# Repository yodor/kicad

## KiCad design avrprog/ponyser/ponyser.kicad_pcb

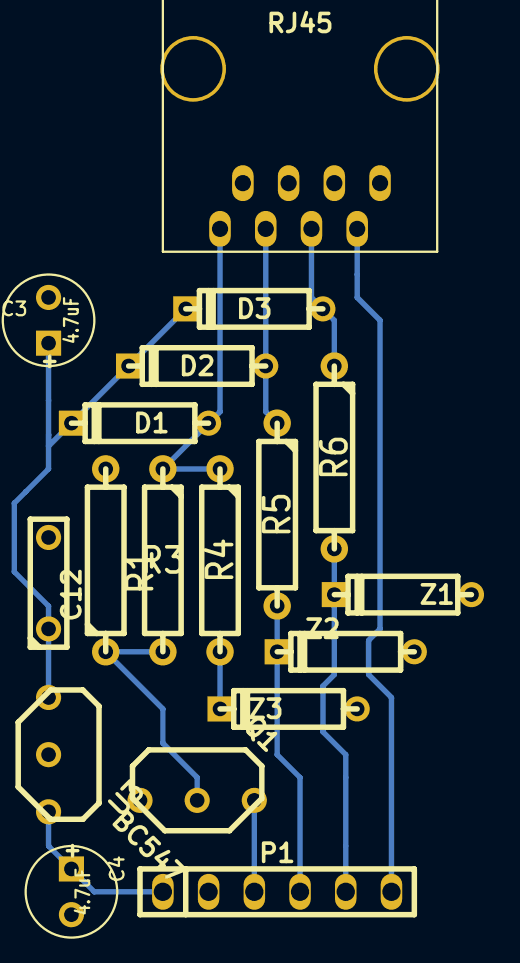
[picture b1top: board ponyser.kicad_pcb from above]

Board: 2 copper layers, 18 parts (0 on the bottom side), 12 nets.

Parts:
C3, C4: 4.7uF; C1V5
C12: 100nF; C2
D1, D2, D3: DIODE; D3
J1: RJ45; RJ45_8
P1: CONN_6; PIN_ARRAY-6X1
Q1: BC547; TO92
R1: 15K; R4
R3: 10K; R4
R4, R5, R6: 4.7K; R4
U3: LM2936Z-5; LM2931
Z1, Z2, Z3: 5.1V; D3

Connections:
GND: C3.2, C4.2, C12.2, J1.1, J1.3, J1.5, J1.7, P1.1, Q1.1, R1.2, U3.GND, Z1.1, Z2.1, Z3.1
unnamed: D1.1, J1.8, R3.1, R4.1
unnamed: Q1.2, R1.1, R3.2
unnamed: P1.6, Q1.3
unnamed: J1.2, P1.5
unnamed: D2.1, J1.6, R5.1
unnamed: D3.1, J1.4, R6.1
unnamed: C3.1, C12.1, D1.2, D2.2, D3.2, U3.VI
unnamed: P1.3, R6.2, Z1.2
unnamed: P1.4, R5.2, Z2.2
unnamed: R4.2, Z3.2
VCC: C4.1, P1.2, U3.VO

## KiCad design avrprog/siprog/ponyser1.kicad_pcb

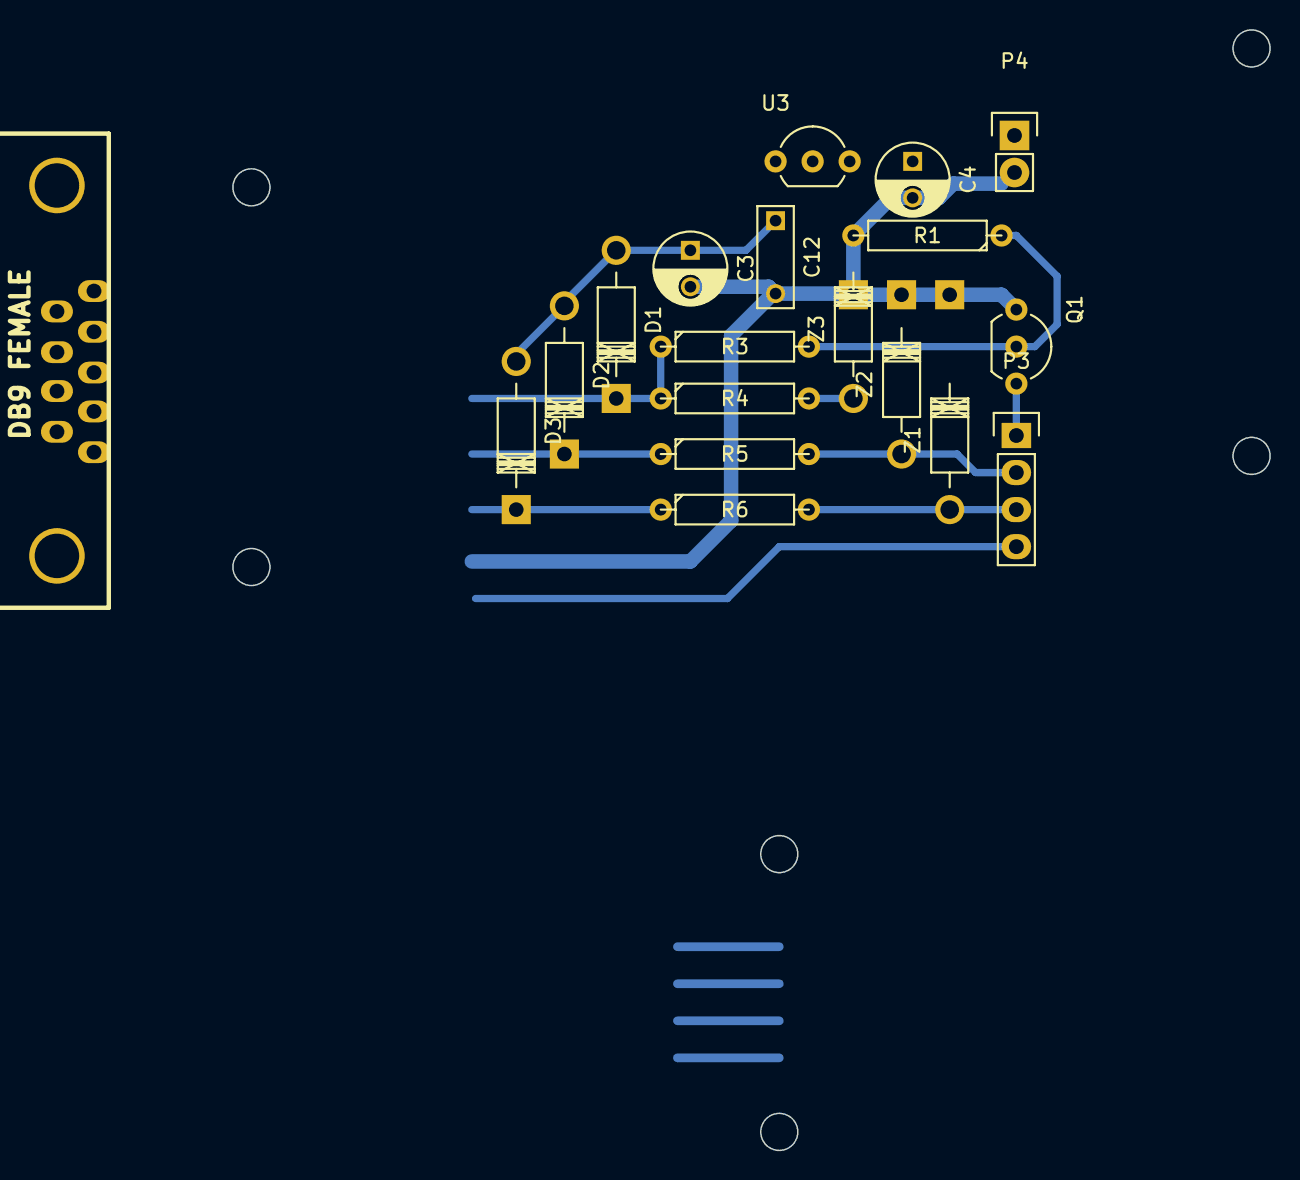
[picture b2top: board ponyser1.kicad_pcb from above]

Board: 2 copper layers, 71.1 x 76.8 mm, 19 parts (0 on the bottom side), 12 nets.

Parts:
C3, C4: 47uF; C_Radial_D5_L11_P2.5
C12: 100nF; C_Rect_L7_W2.5_P5
D1: 1N4148; Diode_DO-41_SOD81_Horizontal_RM10
D2, D3: DIODE; Diode_DO-41_SOD81_Horizontal_RM10
J1: DB9 FEMALE; DB9MC
P3: CONN_4; Pin_Header_Straight_1x04
P4: CONN_2; Pin_Header_Straight_1x02
Q1: BC547; TO-92_Inline_Wide
R1: 15K; R4
R3: 10K; R4
R4, R5, R6: 4.7K; R4
U3: LM2936Z-5; TO-92_Inline_Wide
Z1, Z2, Z3: 5.1V; Diode_DO-41_SOD81_Horizontal_RM10

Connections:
/CTS: J1.8, P3.4
/DTR: D3.1, J1.4, R6.1
/MOSI: P3.3, R6.2, Z1.2
/RST: P3.1, Q1.3
/RTS: D2.1, J1.7, R5.1
/SCK: P3.2, R5.2, Z2.2
/TX: D1.1, J1.3, R3.1, R4.1
GND: C3.2, C4.2, C12.2, J1.5, P4.2, Q1.1, R1.2, Z1.1, Z2.1, Z3.1
unnamed: C3.1, C12.1, D1.2, D2.2, D3.2
unnamed: Q1.2, R1.1, R3.2
unnamed: R4.2, Z3.2
VCC: C4.1, P4.1

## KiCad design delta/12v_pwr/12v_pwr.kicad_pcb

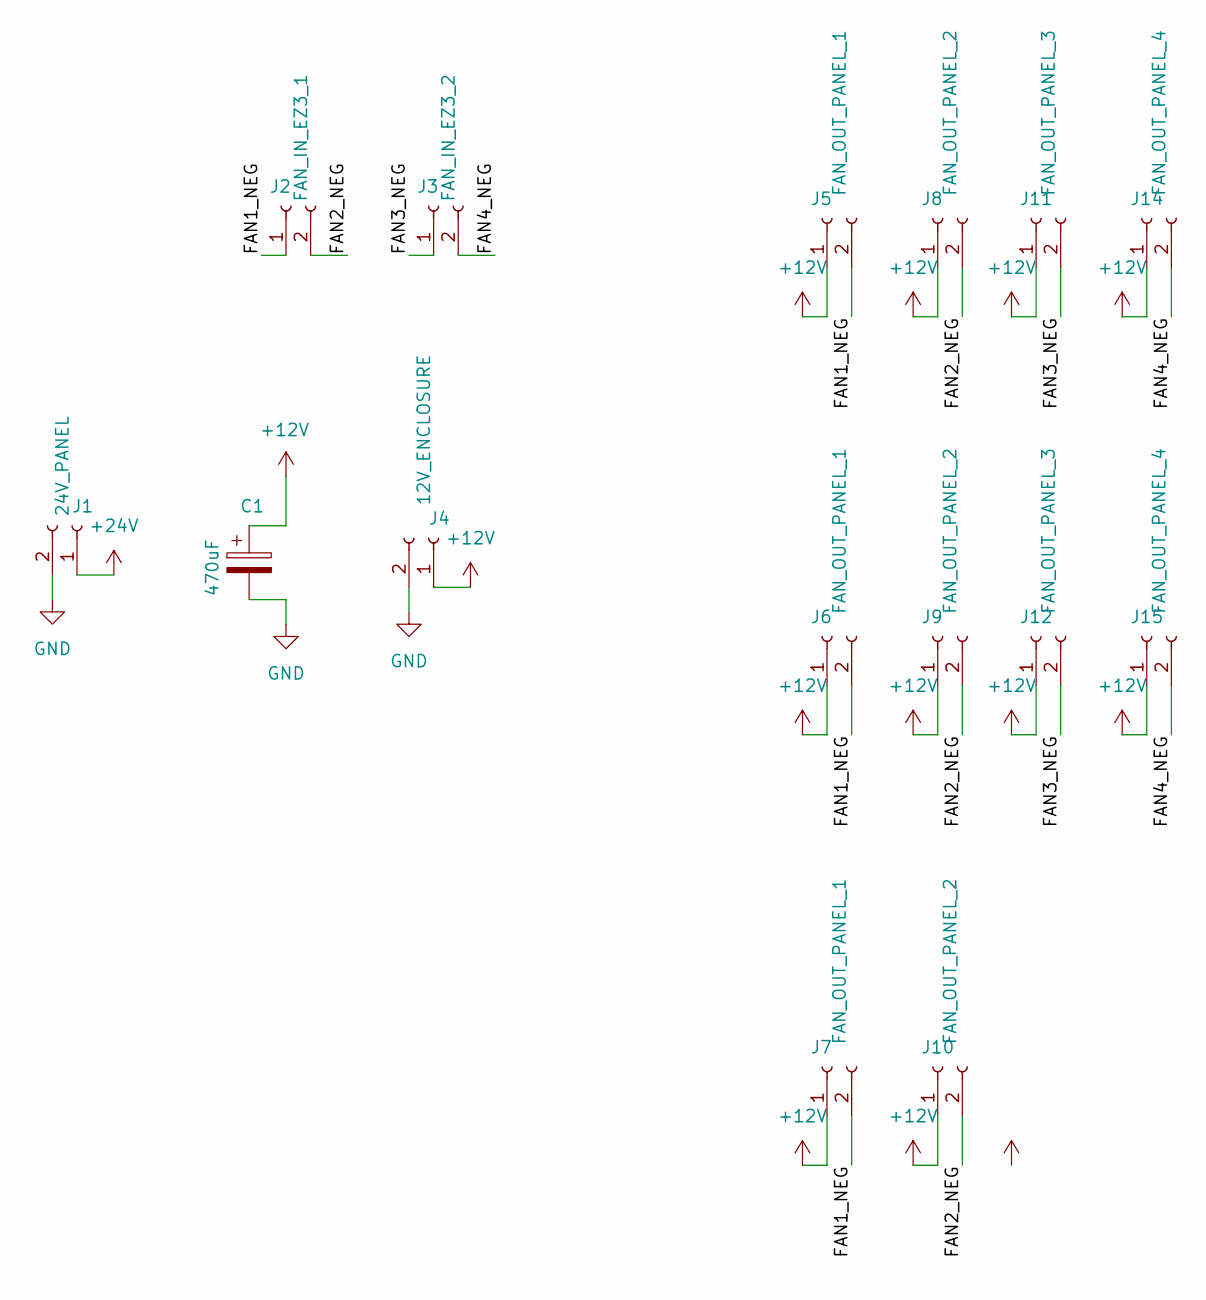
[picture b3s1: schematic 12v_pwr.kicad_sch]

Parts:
C1: 470uF; CP_Radial_D10.0mm_P5.00mm
J1: 24V_PANEL; TerminalBlock_Phoenix_PT-1,5-2-5.0-H_1x02_P5.00mm_Horizontal
J2: FAN_IN_EZ3_1; JST_XH_B2B-XH-A_1x02_P2.50mm_Vertical
J3: FAN_IN_EZ3_2; JST_XH_B2B-XH-A_1x02_P2.50mm_Vertical
J4: 12V_ENCLOSURE; TerminalBlock_Phoenix_PT-1,5-2-5.0-H_1x02_P5.00mm_Horizontal
J5, J6, J7: FAN_OUT_PANEL_1; JST_XH_B2B-XH-A_1x02_P2.50mm_Vertical
J8, J9, J10: FAN_OUT_PANEL_2; JST_XH_B2B-XH-A_1x02_P2.50mm_Vertical
J11, J12: FAN_OUT_PANEL_3; JST_XH_B2B-XH-A_1x02_P2.50mm_Vertical
J14, J15: FAN_OUT_PANEL_4; JST_XH_B2B-XH-A_1x02_P2.50mm_Vertical

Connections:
+12V: C1.1, J4.1, J5.1, J6.1, J7.1, J8.1, J9.1, J10.1, J11.1, J12.1, J14.1, J15.1
+24V: J1.1
/FAN1_NEG: J2.1, J5.2, J6.2, J7.2
/FAN2_NEG: J2.2, J8.2, J9.2, J10.2
/FAN3_NEG: J3.1, J11.2, J12.2
/FAN4_NEG: J3.2, J14.2, J15.2
GND: C1.2, J1.2, J4.2

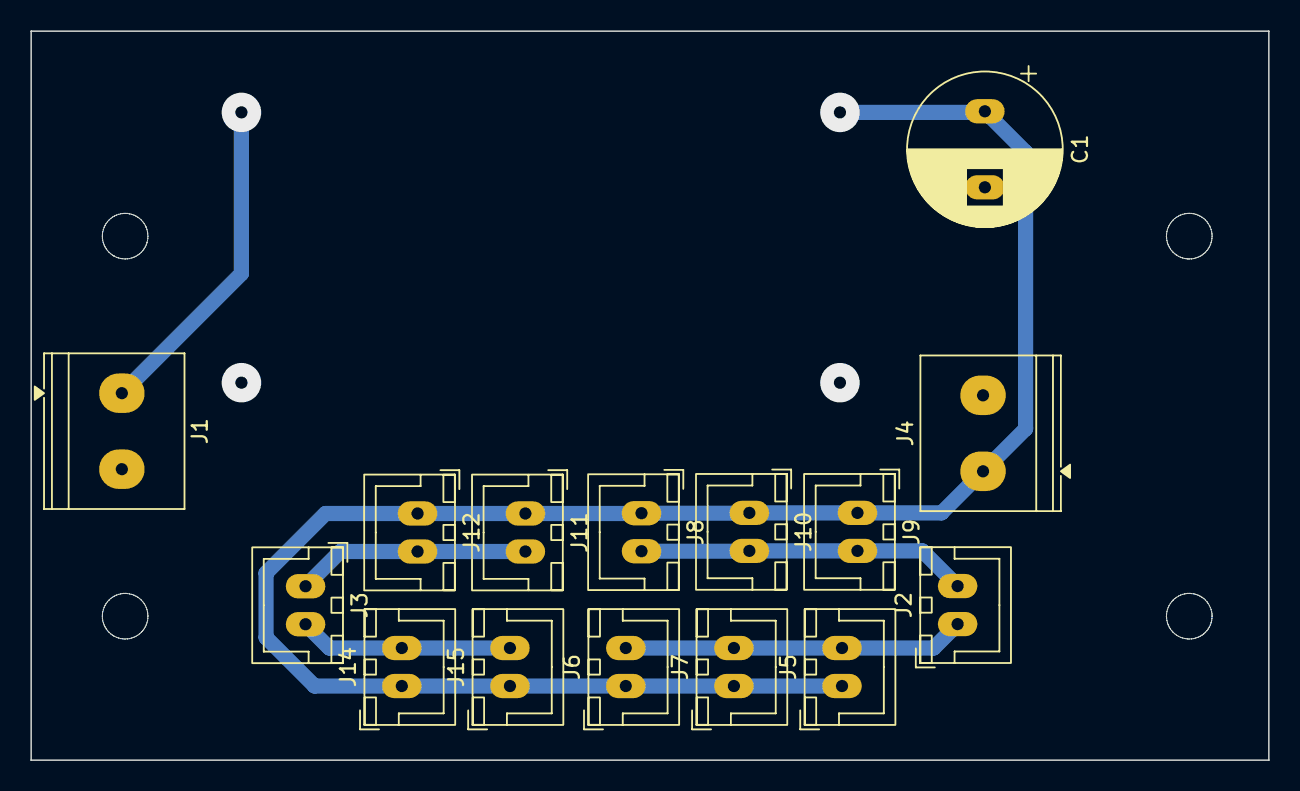
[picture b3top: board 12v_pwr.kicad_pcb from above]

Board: 2 copper layers, 81.4 x 48.0 mm, 15 parts (0 on the bottom side), 6 nets.

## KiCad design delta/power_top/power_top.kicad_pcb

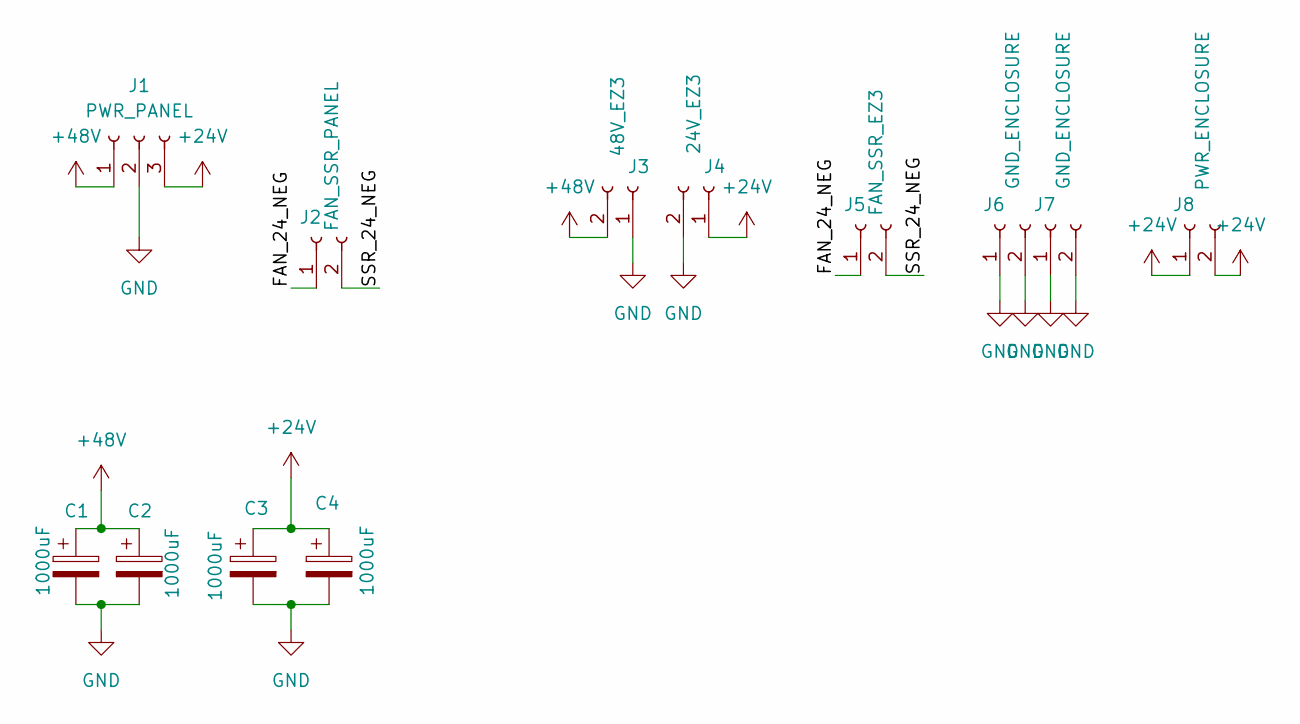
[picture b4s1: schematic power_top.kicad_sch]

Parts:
C1, C2, C3, C4: 1000uF; CP_Radial_D16.0mm_P7.50mm
J1: PWR_PANEL; TE_826576-3_1x03_P3.96mm_Vertical
J2: FAN_SSR_PANEL; TE_826576-2_1x02_P3.96mm_Vertical
J3: 48V_EZ3; TE_826576-2_1x02_P3.96mm_Vertical
J4: 24V_EZ3; TE_826576-2_1x02_P3.96mm_Vertical
J5: FAN_SSR_EZ3; JST_XH_B2B-XH-A_1x02_P2.50mm_Vertical
J6, J7: GND_ENCLOSURE; TE_826576-2_1x02_P3.96mm_Vertical
J8: PWR_ENCLOSURE; TE_826576-2_1x02_P3.96mm_Vertical

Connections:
+24V: C3.1, C4.1, J1.3, J4.1, J8.1, J8.2
+48V: C1.1, C2.1, J1.1, J3.2
/FAN_24_NEG: J2.1, J5.1
/SSR_24_NEG: J2.2, J5.2
GND: C1.2, C2.2, C3.2, C4.2, J1.2, J3.1, J4.2, J6.1, J6.2, J7.1, J7.2

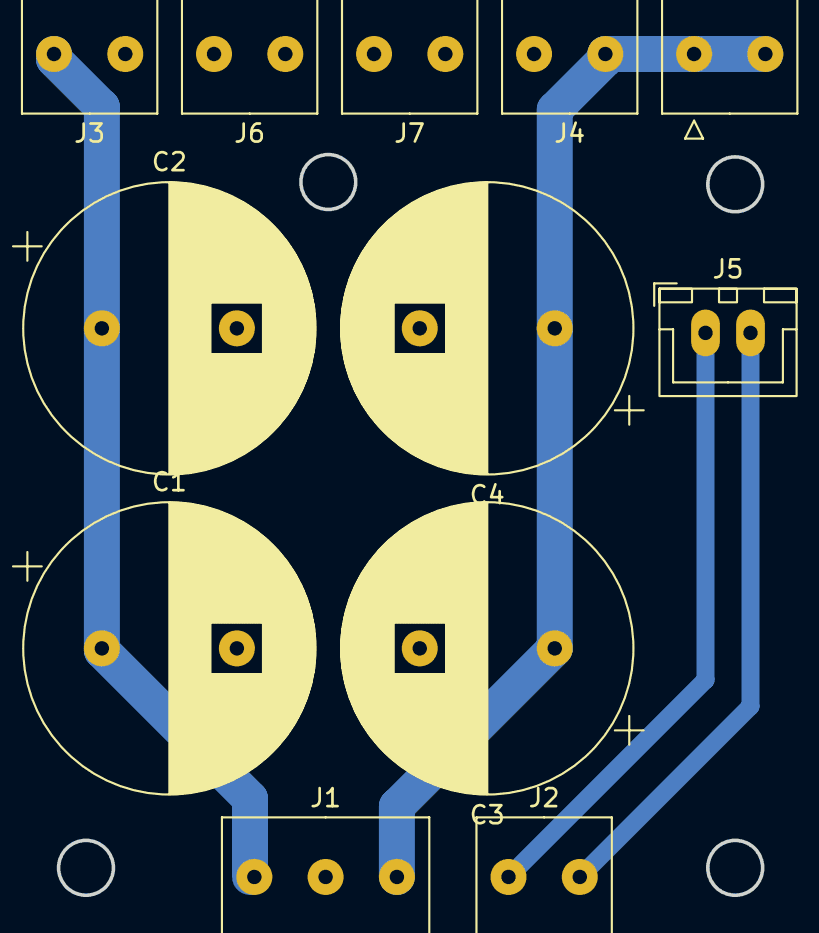
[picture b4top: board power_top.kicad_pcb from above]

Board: 2 copper layers, 12 parts (0 on the bottom side), 5 nets.

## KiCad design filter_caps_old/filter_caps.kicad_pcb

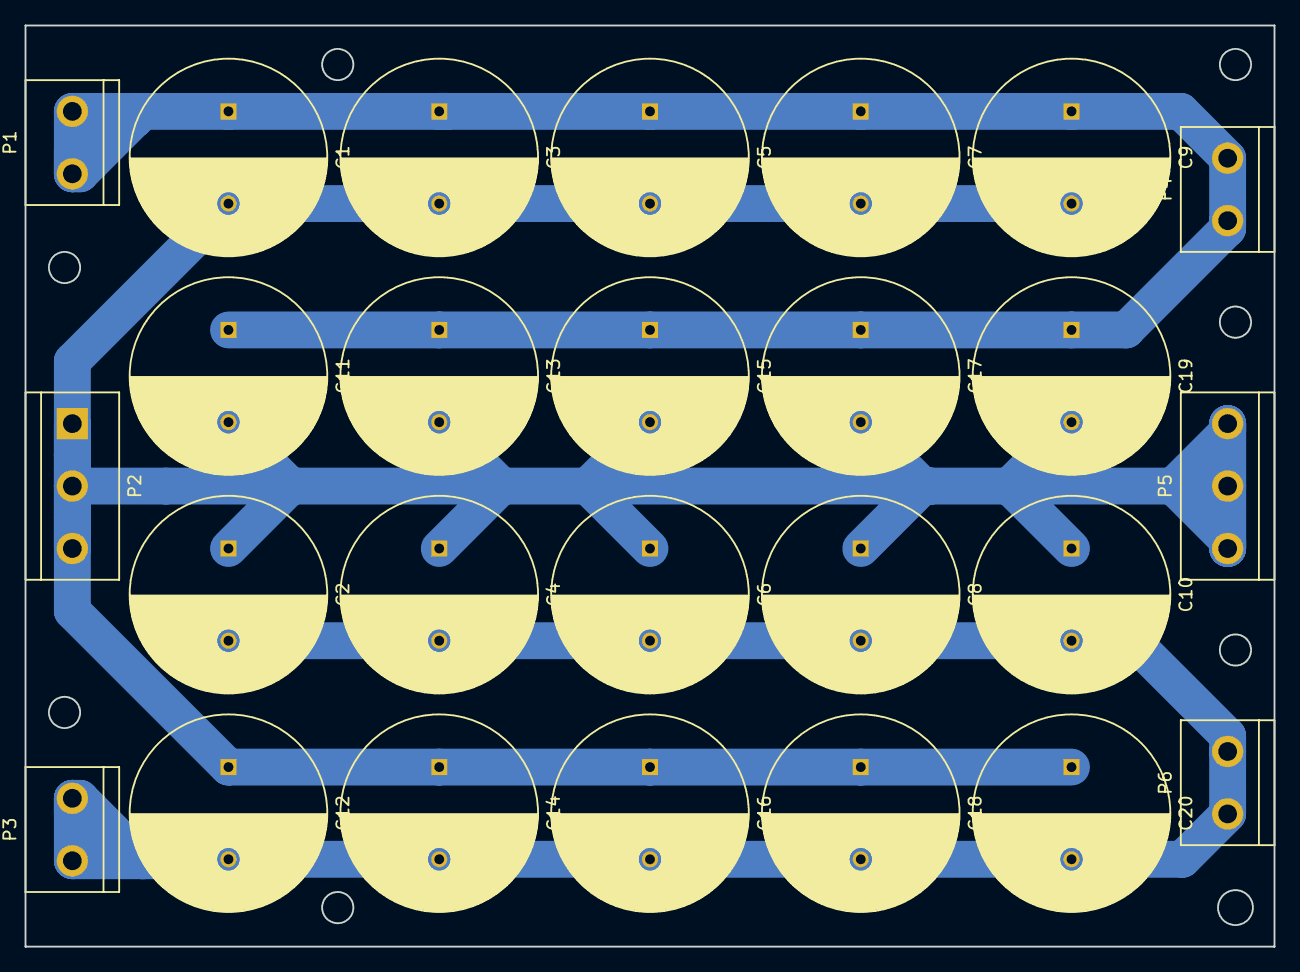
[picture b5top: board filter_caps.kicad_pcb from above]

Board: 2 copper layers, 101.6 x 74.9 mm, 26 parts (0 on the bottom side), 3 nets.

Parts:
C1, C2, C3, C4, C5, C6, C7, C8, C9, C10, C11, C12, C13, C14, C15, C16, C17, C18, C19, C20: CP; C_Radial_D16_L25_P7.5
P1, P3, P4, P6: CONN_01X02; bornier2
P2, P5: CONN_01X03; bornier3

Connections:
/0: C1.2, C2.1, C3.2, C4.1, C5.2, C6.1, C7.2, C8.1, C9.2, C10.1, C11.2, C12.1, C13.2, C14.1, C15.2, C16.1, C17.2, C18.1, C19.2, C20.1, P2.1, P2.2, P2.3, P5.1, P5.2, P5.3
/V+: C1.1, C3.1, C5.1, C7.1, C9.1, C11.1, C13.1, C15.1, C17.1, C19.1, P1.1, P1.2, P4.1, P4.2
/V-: C2.2, C4.2, C6.2, C8.2, C10.2, C12.2, C14.2, C16.2, C18.2, C20.2, P3.1, P3.2, P6.1, P6.2

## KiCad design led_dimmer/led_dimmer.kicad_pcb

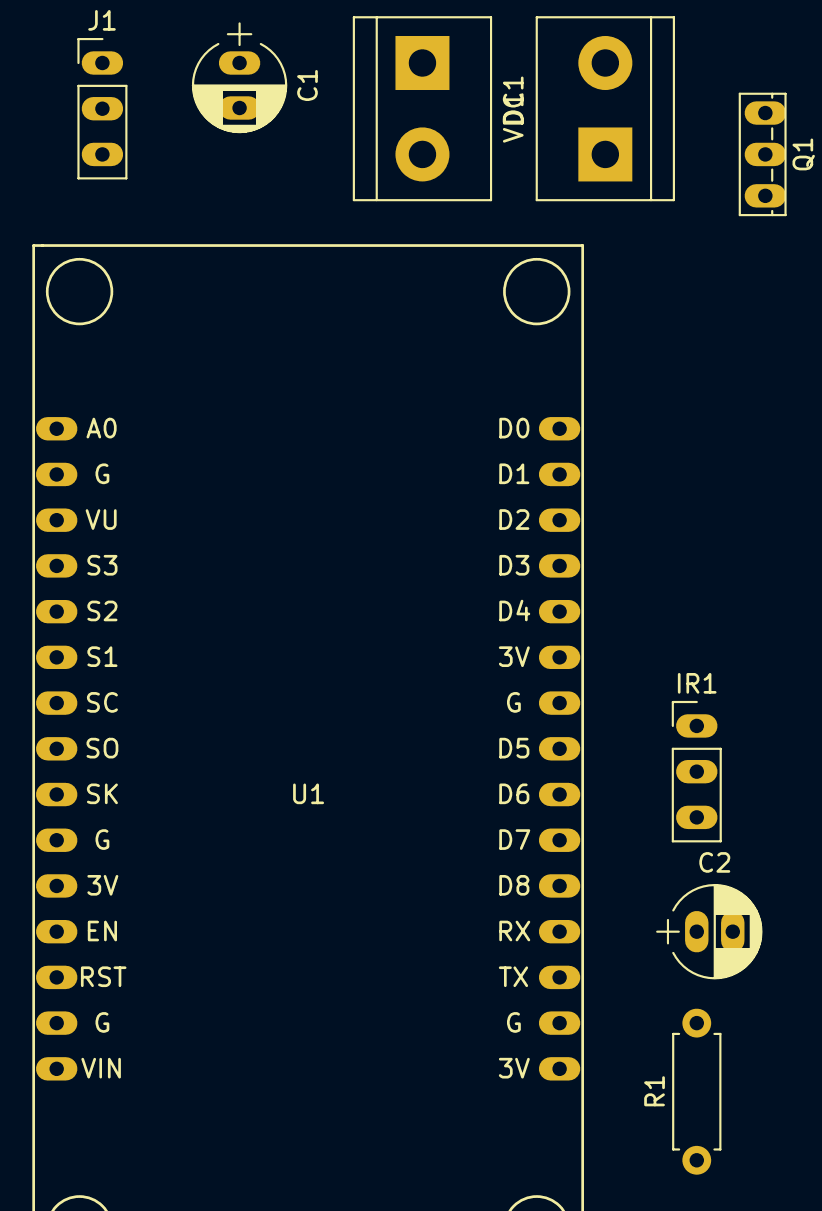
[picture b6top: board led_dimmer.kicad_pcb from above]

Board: 2 copper layers, 9 parts (0 on the bottom side), 8 nets, no tracks yet.

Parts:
C1: 47uF; CP_Radial_D5.0mm_P2.50mm
C2: 4.7uF; CP_Radial_D5.0mm_P2.00mm
D1: LED_Series; TerminalBlock_bornier-2_P5.08mm
IR1: CONN_3; Pin_Header_Straight_1x03_Pitch2.54mm
J1: Conn_01x03; Pin_Header_Straight_1x03_Pitch2.54mm
Q1: Q_NMOS_GDS; TO-251_IPAK_Vertical
R1: 100R; R_Axial_DIN0207_L6.3mm_D2.5mm_P7.62mm_Horizontal
U1: NodeMCU1.0(ESP-12E); NodeMCU-LoLinV3
VDC1: CONN_2; TerminalBlock_bornier-2_P5.08mm

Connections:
+5V: J1.3, U1.3
+12V: C1.1, D1.2, J1.1, VDC1.1
/3.3V: R1.1, U1.16
/IR: IR1.1, U1.23
/LED_PWM: Q1.1, U1.20
GND: C1.2, C2.2, IR1.3, J1.2, Q1.3, U1.2, VDC1.2
unnamed: C2.1, IR1.2, R1.2
unnamed: D1.1, Q1.2

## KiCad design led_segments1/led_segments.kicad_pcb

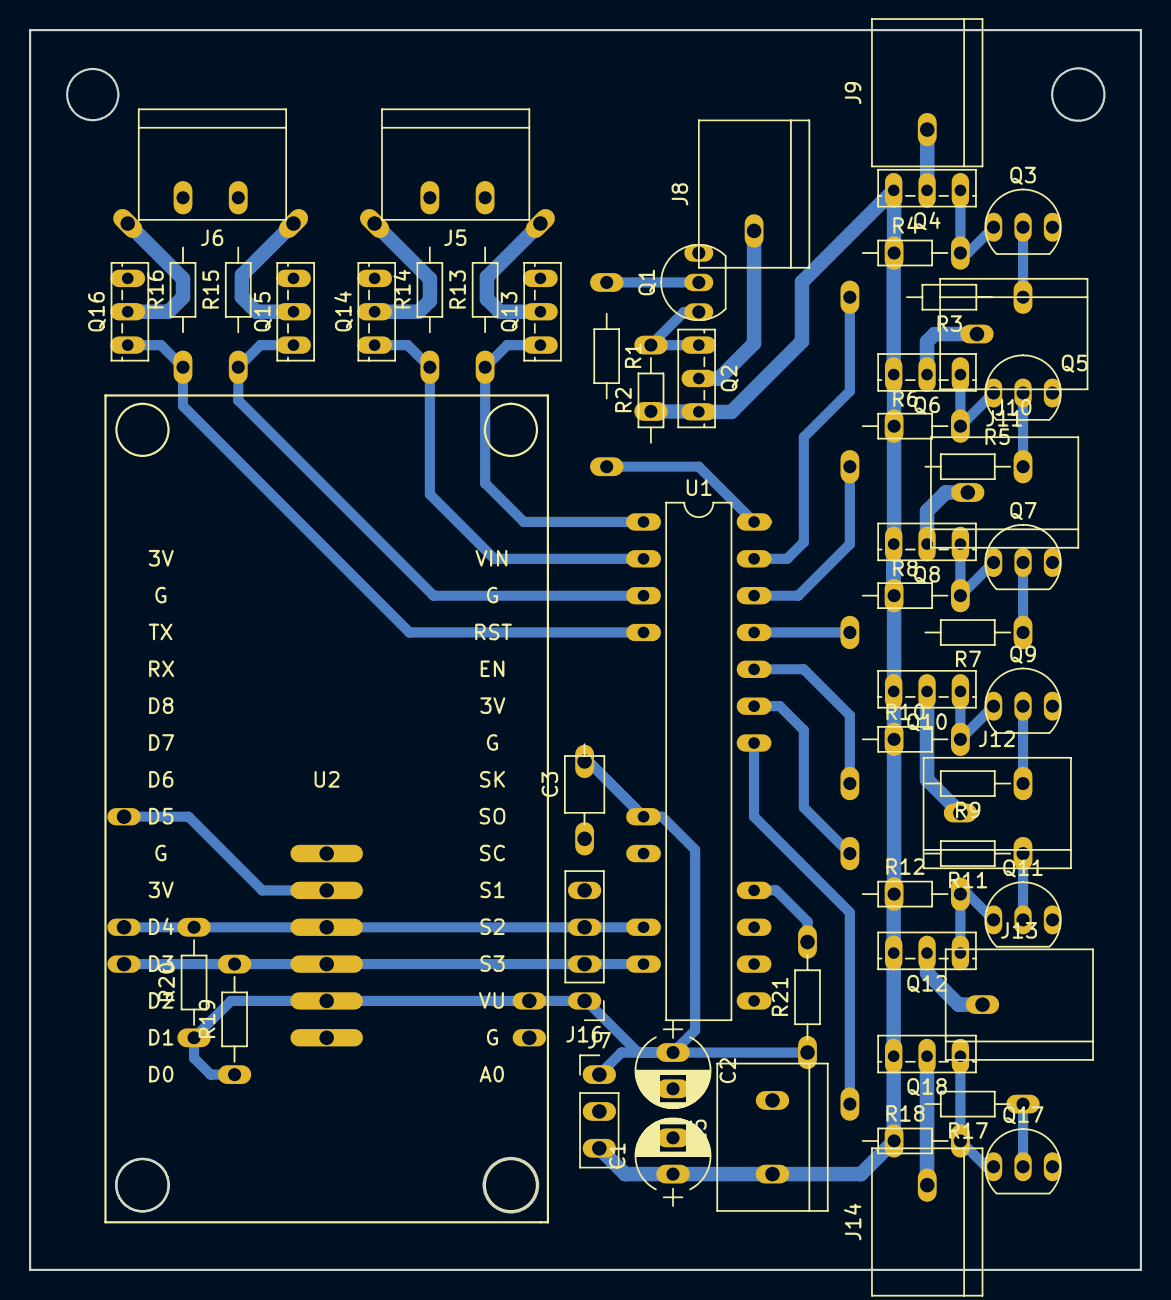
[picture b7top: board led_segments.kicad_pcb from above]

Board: 2 copper layers, 76.6 x 85.5 mm, 57 parts (1 on the bottom side), 43 nets.

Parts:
C1, C2: 47uF; CP_Radial_D5.0mm_P2.50mm
C3: 100n; C_Axial_L3.8mm_D2.6mm_P7.50mm_Horizontal
J1: Conn_01x06_Female; Pin_Header_Angled_1x06_Pitch2.54mm
J5, J6, J8, J9, J10, J11, J12, J13, J14, J15: Conn_01x02; TerminalBlock_bornier-2_P5.08mm
J7: Conn_01x03; Pin_Header_Straight_1x03_Pitch2.54mm
J16: Conn_01x04; Pin_Header_Straight_1x04_Pitch2.54mm
Q1, Q3, Q5, Q7, Q9, Q11, Q17: BC547; TO-92_Inline_Narrow_Oval
Q2, Q4, Q6, Q8, Q10, Q12, Q18: IRFU9024N; TO-251_IPAK_Vertical
Q13, Q14, Q15, Q16: IRLU024N; TO-251_IPAK_Vertical
R1, R2, R3, R4, R6, R8, R10, R12, R13, R14, R15, R18, R21: 10K; R_Axial_DIN0204_L3.6mm_D1.6mm_P7.62mm_Horizontal
R5, R7, R9, R11, R17: R; R_Axial_DIN0204_L3.6mm_D1.6mm_P7.62mm_Horizontal
R16: 10k; R_Axial_DIN0204_L3.6mm_D1.6mm_P7.62mm_Horizontal
R19, R20: 2.2K; R_Axial_DIN0204_L3.6mm_D1.6mm_P7.62mm_Horizontal
U1: MCP23017; DIP-28_W7.62mm_LongPads
U2: NodeMCU1.0(ESP-12E); NodeMCU-LoLinV3

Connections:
+5V: C2.1, C3.2, J1.2, J7.1, J16.1, R19.1, R20.1, R21.1, U1.9, U2.3
+12V: C1.1, J7.3, J15.1, Q2.3, Q4.3, Q6.3, Q8.3, Q10.3, Q12.3, Q18.3, R2.1, R4.1, R6.1, R8.1, R10.1, R12.1, R18.1
/SCL: J1.4, J16.3, R20.2, U1.12, U2.26
/SDA: J1.3, J16.2, R19.2, U1.13, U2.27
/SQW: J1.5, U2.23
/digit1_EN: Q13.1, R13.1, U1.1
/digit1_out: J5.1, Q13.2
/digit2_EN: Q14.1, R14.1, U1.2
/digit2_out: J5.2, Q14.2
/digit3_EN: Q15.1, R15.1, U1.3
/digit3_out: J6.1, Q15.2
/digit4_EN: Q16.1, R16.1, U1.4
/digit4_out: J6.2, Q16.2
/segA_EN: R1.2, U1.28
/segA_pwr: J8.1, Q2.2
/segB_EN: R3.2, U1.27
/segB_pwr: J9.1, Q4.2
/segC_EN: R5.2, U1.26
/segC_pwr: J10.2, Q6.2
/segD_EN: R7.2, U1.25
/segD_pwr: J11.1, Q8.2
/segE_EN: R9.2, U1.24
/segE_pwr: J12.1, Q10.2
/segF_EN: R11.2, U1.23
/segF_pwr: J13.1, Q12.2
/segG_EN: R17.2, U1.22
/segG_pwr: J14.2, Q18.2
GND: C1.2, C2.2, C3.1, J1.1, J7.2, J15.2, J16.4, Q1.3, Q3.3, Q5.3, Q7.3, Q9.3, Q11.3, Q13.3, Q14.3, Q15.3, Q16.3, Q17.3, R13.2, R14.2, R15.2, R16.2, U1.10, U1.15, U1.16, U1.17, U2.2
unnamed: Q1.1, Q2.1, R2.2
unnamed: Q1.2, R1.1
unnamed: Q3.1, Q4.1, R4.2
unnamed: Q3.2, R3.1
unnamed: Q5.1, Q6.1, R6.2
unnamed: Q5.2, R5.1
unnamed: Q7.1, Q8.1, R8.2
unnamed: Q7.2, R7.1
unnamed: Q9.2, R9.1
unnamed: Q9.1, Q10.1, R10.2
unnamed: Q11.1, Q12.1, R12.2
unnamed: Q11.2, R11.1
unnamed: Q17.1, Q18.1, R18.2
unnamed: Q17.2, R17.1
unnamed: R21.2, U1.18
